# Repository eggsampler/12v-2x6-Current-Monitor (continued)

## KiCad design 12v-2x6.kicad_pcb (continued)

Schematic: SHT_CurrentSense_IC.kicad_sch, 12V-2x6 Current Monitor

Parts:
C1, C2: 0.1u; C_0402_1005Metric
R8, R9: 10R; R_0402_1005Metric
R10: 10k; R_0402_1005Metric
U1: INA238; VSSOP-10_3x3mm_P0.5mm

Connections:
+5VP: C1.1, R10.2, U1.6 (VS); also elsewhere on the board
/12V-2x6 Connectors/12V_OUT1: U1.8 (Vbus); also elsewhere on the board
/Alert Isolation/ALERT_IN1: R10.1, U1.3 (~Alert); also elsewhere on the board
/Current Sensing/CurrentSense1/IN+: R8.1; also elsewhere on the board
/Current Sensing/CurrentSense1/IN-: R9.1; also elsewhere on the board
/Current Sensing/SCL1: U1.5 (SCL); also elsewhere on the board
/Current Sensing/SDA1: U1.4 (SDA); also elsewhere on the board
GND1: C1.2, U1.1 (A1), U1.2 (A0), U1.7 (GND); also elsewhere on the board
unnamed: C2.1, R8.2, U1.10 (Vin+)
unnamed: C2.2, R9.2, U1.9 (Vin-)

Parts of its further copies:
C3, C4, C5, C6, C7, C8, C9, C10, C11, C12: 0.1u; C_0402_1005Metric
R11, R12, R14, R15, R17, R18, R20, R21, R23, R24: 10R; R_0402_1005Metric
R13, R16, R19, R22, R25: 10k; R_0402_1005Metric
U2, U3, U4, U5, U6: INA238; VSSOP-10_3x3mm_P0.5mm

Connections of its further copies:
+5VP: C3.1, C5.1, C7.1, C9.1, C11.1, R13.2, R16.2, R19.2, R22.2, R25.2, U2.2 (A0), U2.6 (VS), U3.6 (VS), U4.1 (A1), U4.6 (VS), U5.1 (A1), U5.2 (A0), U5.6 (VS), U6.1 (A1), U6.6 (VS); also elsewhere on the board
/12V-2x6 Connectors/12V_OUT2: U2.8 (Vbus); also elsewhere on the board
/12V-2x6 Connectors/12V_OUT3: U3.8 (Vbus); also elsewhere on the board
/12V-2x6 Connectors/12V_OUT4: U4.8 (Vbus); also elsewhere on the board
/12V-2x6 Connectors/12V_OUT5: U5.8 (Vbus); also elsewhere on the board
/12V-2x6 Connectors/12V_OUT6: U6.8 (Vbus); also elsewhere on the board
/Alert Isolation/ALERT_IN2: R13.1, U2.3 (~Alert); also elsewhere on the board
/Alert Isolation/ALERT_IN3: R16.1, U3.3 (~Alert); also elsewhere on the board
/Alert Isolation/ALERT_IN4: R19.1, U4.3 (~Alert); also elsewhere on the board
/Alert Isolation/ALERT_IN5: R22.1, U5.3 (~Alert); also elsewhere on the board
/Alert Isolation/ALERT_IN6: R25.1, U6.3 (~Alert); also elsewhere on the board
/Current Sensing/CurrentSense2/IN+: R11.1; also elsewhere on the board
/Current Sensing/CurrentSense2/IN-: R12.1; also elsewhere on the board
/Current Sensing/CurrentSense3/IN+: R14.1; also elsewhere on the board
/Current Sensing/CurrentSense3/IN-: R15.1; also elsewhere on the board
/Current Sensing/CurrentSense4/IN+: R17.1; also elsewhere on the board
/Current Sensing/CurrentSense4/IN-: R18.1; also elsewhere on the board
/Current Sensing/CurrentSense5/IN+: R20.1; also elsewhere on the board
/Current Sensing/CurrentSense5/IN-: R21.1; also elsewhere on the board
/Current Sensing/CurrentSense6/IN+: R23.1; also elsewhere on the board
/Current Sensing/CurrentSense6/IN-: R24.1; also elsewhere on the board
/Current Sensing/SCL1: U2.5 (SCL), U3.5 (SCL), U4.5 (SCL), U5.5 (SCL), U6.5 (SCL); also elsewhere on the board
/Current Sensing/SDA1: U2.4 (SDA), U3.2 (A0), U3.4 (SDA), U4.4 (SDA), U5.4 (SDA), U6.2 (A0), U6.4 (SDA); also elsewhere on the board
GND1: C3.2, C5.2, C7.2, C9.2, C11.2, U2.1 (A1), U2.7 (GND), U3.1 (A1), U3.7 (GND), U4.2 (A0), U4.7 (GND), U5.7 (GND), U6.7 (GND); also elsewhere on the board
unnamed: C4.1, R11.2, U2.10 (Vin+)
unnamed: C4.2, R12.2, U2.9 (Vin-)
unnamed: C6.1, R14.2, U3.10 (Vin+)
unnamed: C6.2, R15.2, U3.9 (Vin-)
unnamed: C8.1, R17.2, U4.10 (Vin+)
unnamed: C8.2, R18.2, U4.9 (Vin-)
unnamed: C10.1, R20.2, U5.10 (Vin+)
unnamed: C10.2, R21.2, U5.9 (Vin-)
unnamed: C12.1, R23.2, U6.10 (Vin+)
unnamed: C12.2, R24.2, U6.9 (Vin-)

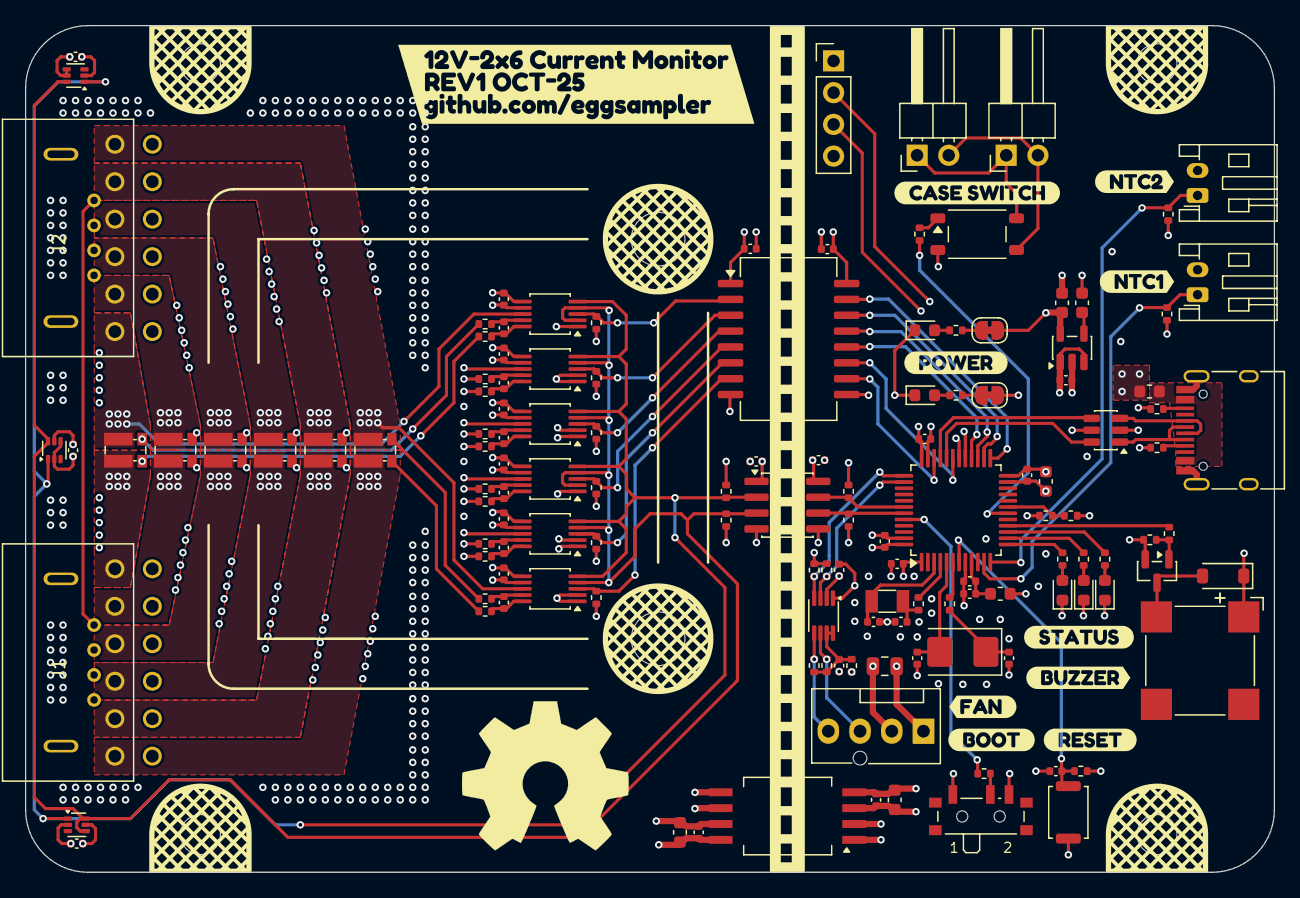
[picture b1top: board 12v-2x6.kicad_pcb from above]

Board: 6 copper layers, 100.0 x 67.8 mm, 152 parts (1 on the bottom side), 112 nets.

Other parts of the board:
kibuzzard-68F03828: G***; kibuzzard-68F03828
kibuzzard-689C047C: G***; kibuzzard-689C047C
kibuzzard-6896FD1A: G***; kibuzzard-6896FD1A
kibuzzard-6896FD13: G***; kibuzzard-6896FD13
kibuzzard-68974EEA: G***; kibuzzard-68974EEA
kibuzzard-68974EFC: G***; kibuzzard-68974EFC
kibuzzard-68974F1C: G***; kibuzzard-68974F1C
kibuzzard-68974F03: G***; kibuzzard-68974F03
kibuzzard-68974FED: G***; kibuzzard-68974FED
kibuzzard-68980501: G***; kibuzzard-68980501

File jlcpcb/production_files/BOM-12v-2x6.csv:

Comment,Designator,Footprint,LCSC,Quantity
0,"R27,R28",R_0402_1005Metric,C17168,2
0.1u,"C1,C10,C11,C12,C13,C14,C15,C16,C17,C2,C20,C26,C27,C29,C3,C30,C31,C32,C36,C37,C39,C4,C40,C41,C5,C6,C7,C8,C9",C_0402_1005Metric,C307331,29
100R,R50,R_0402_1005Metric,C25076,1
100k,R51,R_0402_1005Metric,C25741,1
10R,"R11,R12,R14,R15,R17,R18,R20,R21,R23,R24,R8,R9",R_0402_1005Metric,C25077,12
10k,"R10,R13,R16,R19,R22,R25,R26,R39,R40,R49,R7",R_0402_1005Metric,C25744,11
10u,"C19,C25,C28,C35",C_0603_1608Metric,C96446,4
1N4148W,D6,D_SOD-123,C81598,1
1k,"R33,R34,R35,R47,R48",R_0402_1005Metric,C11702,5
1u,"C18,C33",C_0402_1005Metric,C52923,2
2.2k,"R41,R42,R43,R44,R45",R_0402_1005Metric,C25879,5
200k,R46,R_0402_1005Metric,C25764,1
220R,R38,R_0402_1005Metric,C25091,1
22p,"C23,C24",C_0402_1005Metric,C1555,2
22u,C38,C_0805_2012Metric,C45783,1
32.768k FC-135 12.5pF,Y2,Crystal_SMD_3215-2Pin_3.2x1.5mm,C32346,1
33p,"C21,C22",C_0402_1005Metric,C1562,2
3m,"R1,R2,R3,R4,R5,R6",R_Shunt_Vishay_WSKW0612,C1517434,6
470531000,M2,FanPinHeader_1x04_P2.54mm_Vertical,C240840,1
470p,C34,C_0603_1608Metric,C1620,1
5.1k,"R29,R30,R31,R32,R36,R37",R_0402_1005Metric,C25905,6
8M YSX530GA 20pF,Y1,Crystal_SMD_5032-2Pin_5.0x3.2mm,C115962,1
ADuM260N1,U12,SOIC-16W_7.5x12.8mm_P1.27mm,C660709,1
AO3400A,Q1,SOT-23,C20917,1
B0505ST8-W3,U10,SSO-8_6.8x5.9mm_P1.27mm_Clearance8mm,C22751415,1
BLUE,D3,LED_0603_1608Metric,C2290,1
FerriteBead_Small,FB1,L_0603_1608Metric,C1002,1
FerriteBead_Small,FB2,L_0603_1608Metric,C14709,1
GREEN,D2,LED_0603_1608Metric,C89811,1
INA238,"U1,U2,U3,U4,U5,U6",VSSOP-10_3x3mm_P0.5mm,C2868250,6
ISO1540,U11,SOIC-8_3.9x4.9mm_P1.27mm,C179739,1
MIC5219-3.3YM5,U13,SOT-23-5,C29613,1
MLT-8530,BZ1,MagneticBuzzer_CUI_CMT-8504-100-SMT,C94599,1
PCA9306,U14,VSSOP-8_2.3x2mm_P0.5mm,C33196,1
PCM12,SW2,SW_SPDT_PCM12,C221841,1
PH 1x02 2.54,"J4,J5",PinHeader_1x02_P2.54mm_Horizontal,C492410,2
PURPLE,D5,LED_0603_1608Metric,C89811,1
RED,D1,LED_0603_1608Metric,C2286,1
S2B-PH-K 1x02 P2,"J6,J7",JST_PH_S2B-PH-K_1x02_P2.00mm_Horizontal,C157932,2
SKRK,SW1,SW_Push_SPST_NO_Alps_SKRK,C115357,1
STM32F103C8Tx,U7,LQFP-48_7x7mm_P0.5mm,C8734,1
TLP175A,U9,Toshiba_SOIC-4-6_4.4x3.6mm_P1.27mm,C141522,1
TMP102xxDRL,"U15,U16,U17",SOT-563,C99269,3
USBLC6-2SC6,U8,SOT-23-6,C7519,1
USB_C_Receptacle_USB2.0_16P,J3,USB_C_Receptacle_HRO_TYPE-C-31-M-12,C165948,1
WHITE,D4,LED_0603_1608Metric,C2290,1
10164279-124121LF,J2,10164279-124121LF,,1
10164279-124121LF,J1,10164279-124121LF,,1

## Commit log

2025-08-23 Add initial README
2025-09-20 Update & Review
2025-10-17 Minor updates
    Ground changes, small updates
